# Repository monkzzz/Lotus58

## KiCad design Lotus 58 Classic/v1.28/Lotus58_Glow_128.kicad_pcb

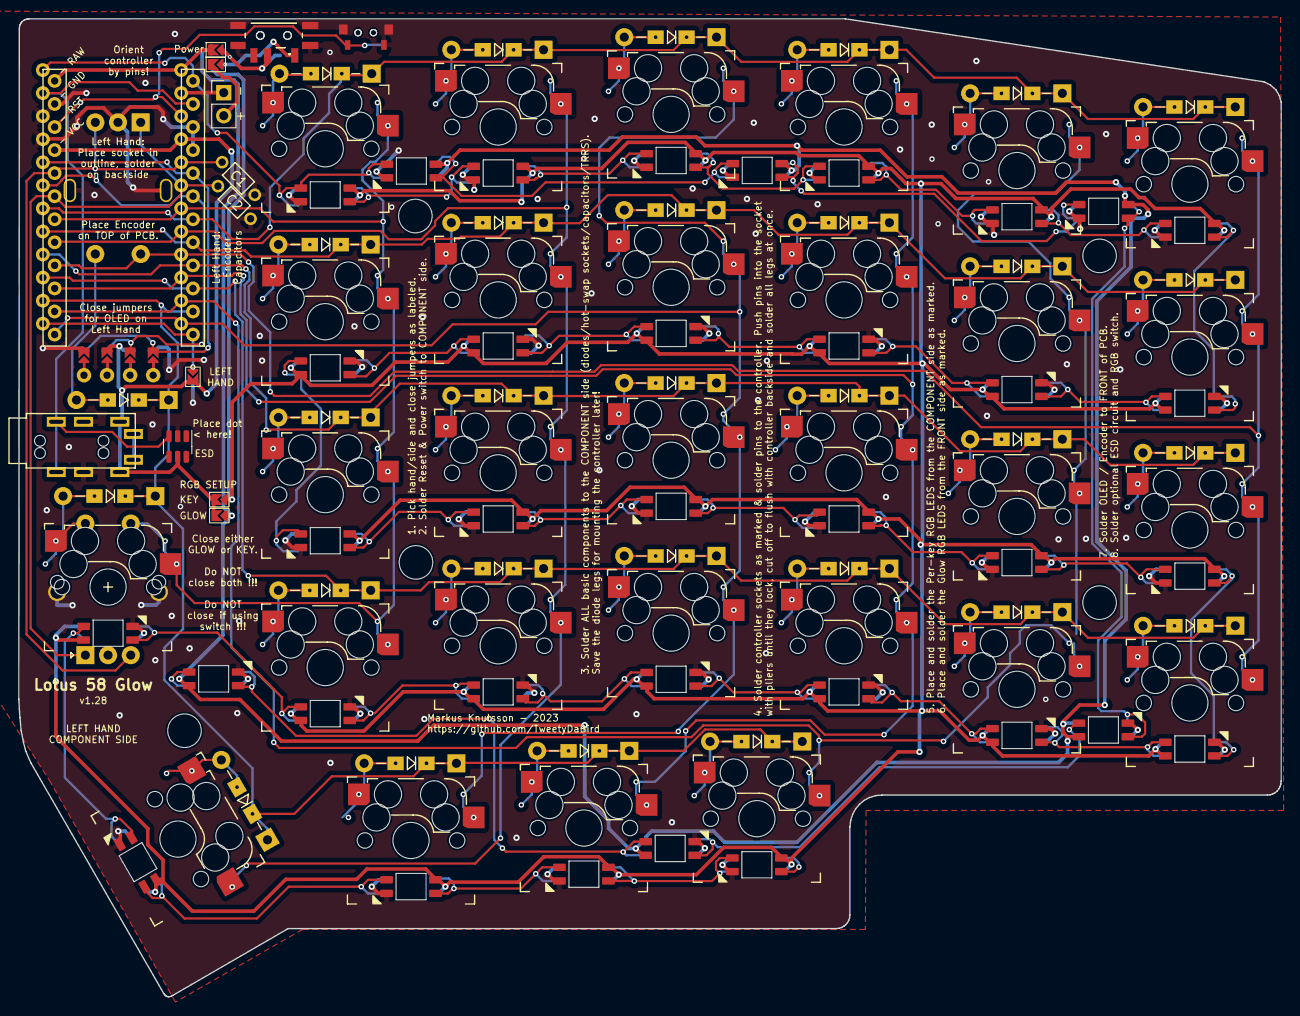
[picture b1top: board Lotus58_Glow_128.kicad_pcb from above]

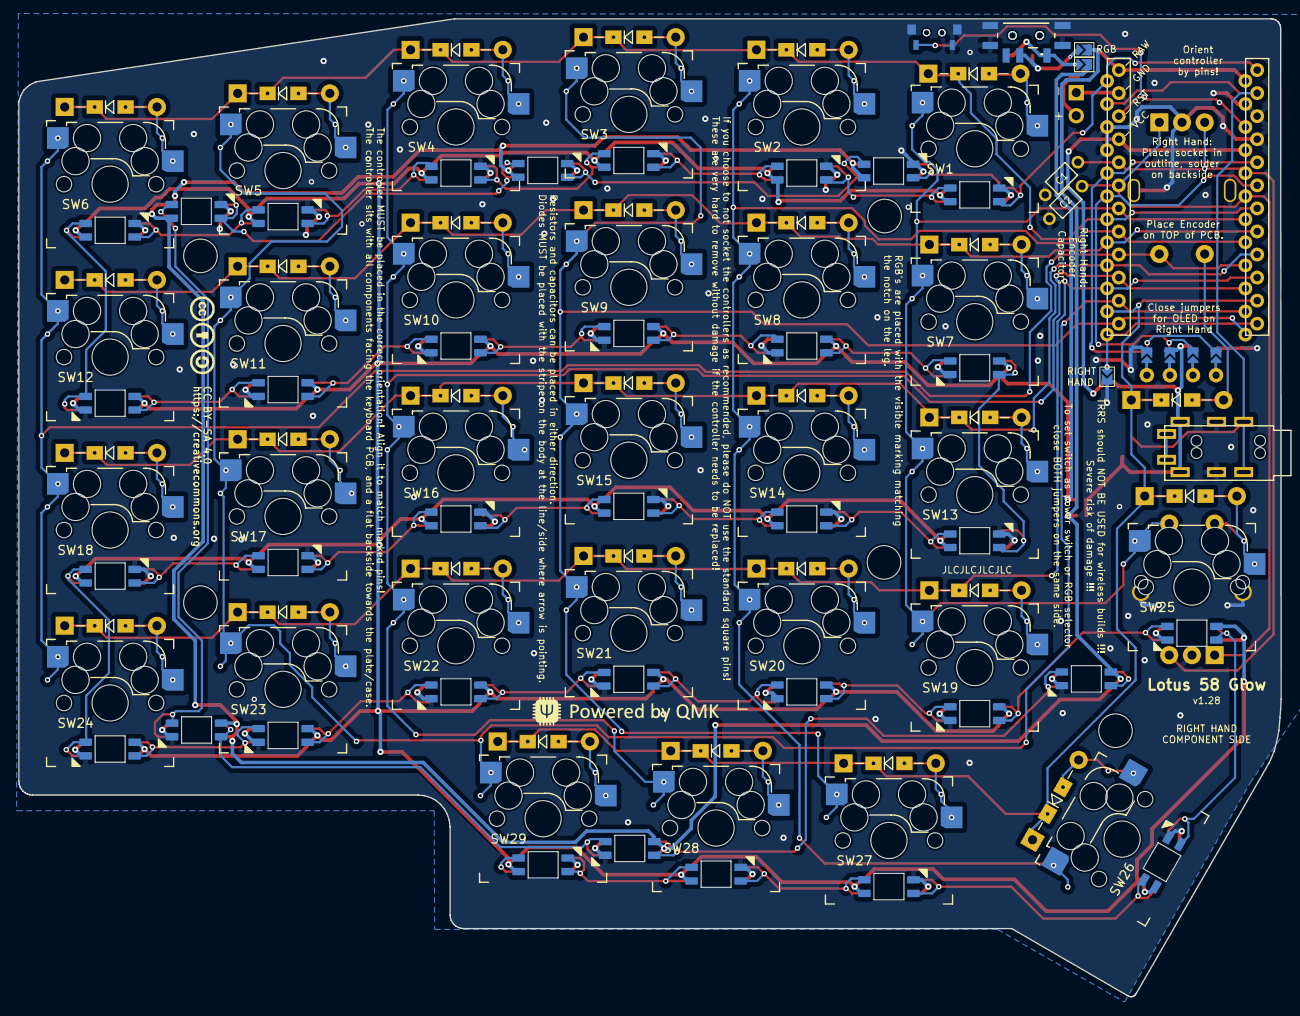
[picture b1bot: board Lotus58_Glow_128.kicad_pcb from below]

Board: 2 copper layers, 139.1 x 107.7 mm, 122 parts (73 on the bottom side), 90 nets.

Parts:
C1, C2: 100nF; RESISTOR_Reversible
D1, D2, D3, D4, D5, D6, D7, D8, D9, D10, D11, D12, D13, D14, D15, D16, D17, D18, D19, D20, D21, D22, D23, D24, D25, D26, D27, D28, D29, D30: 1N4148/1N4148W; Diode_DO35_SOD123
J1: PJ-320A; MJ-4PP-9_alim
J2: Conn_01x02; PinHeader_1x02_P2.54mm_Vertical
JP1, JP4, JP5, JP6, JP7, JP8: FULL; Jumper_min_v2
JP2: LEFT; Jumper_min_v2
JP3: RIGHT; Jumper_min_v2
LED1, LED2, LED3, LED4, LED5, LED6, LED7, LED8, LED9, LED10, LED11, LED12, LED13, LED14, LED15, LED16, LED17, LED18, LED19, LED20, LED21, LED22, LED23, LED24, LED25, LED26, LED27, LED28, LED29, LED30, LED31, LED32, LED33, LED34, LED35: SK6812MINI-E; MX_SK6812MINI-E_REVERSIBLE
Logo1: QMK_Logo; qmk logo
Logo2: CC-BY-SA-4.0; CC_BY_SA_40_line
P1: OLED; SSD1306-0.91-OLED-4pin-128x32 doublesided
RES1, RES2: TS-A002; YTS-A002
S1, S2: MSK12C02
SW1, SW2, SW3, SW4, SW5, SW6, SW7, SW8, SW9, SW10, SW11, SW12, SW13, SW14, SW15, SW16, SW17, SW18, SW19, SW20, SW21, SW22, SW23, SW24, SW25, SW26, SW27, SW28, SW29: Kailh hotswap MX socket; SW_MX_HotSwap_Reversible
SW30: Rotary_Encoder_Switch; RotaryEncoder_Alps_EC11E-Switch_Vertical_H20_special
SW31: Rotary_Encoder_Switch; RotaryEncoder_Alps_EC11E-Switch_Special
TH1, TH2, TH3, TH4, TH5: HOLE; Spacer PCB hole
U1: ProMicro; ProMicro_Reversible_orig
U2: SRV05-4; SOT-23-6

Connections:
/Batt: J2.2, JP4.1
/PWR_GLOW: JP5.2, JP7.1, LED1.1 (VCC), LED2.1 (VCC), LED3.1 (VCC), LED4.1 (VCC), LED5.1 (VCC), LED6.1 (VCC)
/PWR_KEY: JP6.2, JP8.1, LED7.1 (VCC), LED8.1 (VCC), LED9.1 (VCC), LED10.1 (VCC), LED11.1 (VCC), LED12.1 (VCC), LED13.1 (VCC), LED14.1 (VCC), LED15.1 (VCC), LED16.1 (VCC), LED17.1 (VCC), LED18.1 (VCC), LED19.1 (VCC), LED20.1 (VCC), LED21.1 (VCC), LED22.1 (VCC), LED23.1 (VCC), LED24.1 (VCC), LED25.1 (VCC), LED26.1 (VCC), LED27.1 (VCC), LED28.1 (VCC), LED29.1 (VCC), LED30.1 (VCC), LED31.1 (VCC), LED32.1 (VCC), LED33.1 (VCC), LED34.1 (VCC), LED35.1 (VCC)
A: C2.2, SW30.A, SW31.A, U1.19 (A2/PF5)
Alt: D25.2 (A), SW25.2, SW31.S2
B: C1.1, SW30.B, SW31.B, U1.20 (A3/PF4)
Battery: JP1.1, U1.24 (RAW)
DATA: J1.R2, U1.2 (RX1/PD2), U2.3 (IO2)
GND: C1.2, C2.1, J1.R1, J2.1, JP3.1, LED1.3 (GND), LED2.3 (GND), LED3.3 (GND), LED4.3 (GND), LED5.3 (GND), LED6.3 (GND), LED7.3 (GND), LED8.3 (GND), LED9.3 (GND), LED10.3 (GND), LED11.3 (GND), LED12.3 (GND), LED13.3 (GND), LED14.3 (GND), LED15.3 (GND), LED16.3 (GND), LED17.3 (GND), LED18.3 (GND), LED19.3 (GND), LED20.3 (GND), LED21.3 (GND), LED22.3 (GND), LED23.3 (GND), LED24.3 (GND), LED25.3 (GND), LED26.3 (GND), LED27.3 (GND), LED28.3 (GND), LED29.3 (GND), LED30.3 (GND), LED31.3 (GND), LED32.3 (GND), LED33.3 (GND), LED34.3 (GND), LED35.3 (GND), P1.1 (GND), RES1.2, RES1.3, RES2.2, RES2.3, S1.MP (GND), S2.MP (GND), SW30.C, SW30.MP1 (GND), SW30.MP2 (GND), SW31.C, SW31.MP1 (GND), SW31.MP2 (GND), U1.3 (GND), U1.4 (GND), U1.23 (GND), U2.2 (VN)
Hand: JP2.2, JP3.2, U1.12 (9/PB5)
LED: LED1.4 (DIN), LED7.4 (DIN), U1.1 (TX0/PD3)
unnamed: D1.2 (A), SW1.2
unnamed: D2.2 (A), SW2.2
unnamed: D3.2 (A), SW3.2
unnamed: D4.2 (A), SW4.2
unnamed: D5.2 (A), SW5.2
unnamed: D6.2 (A), SW6.2
unnamed: D7.2 (A), SW7.2
unnamed: D8.2 (A), SW8.2
unnamed: D9.2 (A), SW9.2
unnamed: D10.2 (A), SW10.2
unnamed: D11.2 (A), SW11.2
unnamed: D12.2 (A), SW12.2
unnamed: D13.2 (A), SW13.2
unnamed: D14.2 (A), SW14.2
unnamed: D15.2 (A), SW15.2
unnamed: D16.2 (A), SW16.2
unnamed: D17.2 (A), SW17.2
unnamed: D18.2 (A), SW18.2
unnamed: D19.2 (A), SW19.2
unnamed: D20.2 (A), SW20.2
unnamed: D21.2 (A), SW21.2
unnamed: D22.2 (A), SW22.2
unnamed: D23.2 (A), SW23.2
unnamed: D24.2 (A), SW24.2
unnamed: D26.2 (A), SW26.2
unnamed: D27.2 (A), SW27.2
unnamed: D28.2 (A), SW28.2
unnamed: D29.2 (A), SW29.2
unnamed: D30.2 (A), SW30.S1
unnamed: JP1.2, JP7.2, S1.COM, S2.COM
unnamed: JP4.2, JP8.2, S1.NC, S2.NC
unnamed: LED1.2 (DOUT), LED2.4 (DIN)
unnamed: LED2.2 (DOUT), LED3.4 (DIN)
unnamed: LED3.2 (DOUT), LED4.4 (DIN)
unnamed: LED4.2 (DOUT), LED5.4 (DIN)
unnamed: LED5.2 (DOUT), LED6.4 (DIN)
unnamed: LED7.2 (DOUT), LED8.4 (DIN)
unnamed: LED8.2 (DOUT), LED9.4 (DIN)
unnamed: LED9.2 (DOUT), LED10.4 (DIN)
unnamed: LED10.2 (DOUT), LED11.4 (DIN)
unnamed: LED11.2 (DOUT), LED12.4 (DIN)
unnamed: LED12.2 (DOUT), LED18.4 (DIN)
unnamed: LED13.4 (DIN), LED14.2 (DOUT)
unnamed: LED13.2 (DOUT), LED19.4 (DIN)
unnamed: LED14.4 (DIN), LED15.2 (DOUT)
unnamed: LED15.4 (DIN), LED16.2 (DOUT)
unnamed: LED16.4 (DIN), LED17.2 (DOUT)
unnamed: LED17.4 (DIN), LED18.2 (DOUT)
unnamed: LED19.2 (DOUT), LED20.4 (DIN)
unnamed: LED20.2 (DOUT), LED21.4 (DIN)
unnamed: LED21.2 (DOUT), LED22.4 (DIN)
unnamed: LED22.2 (DOUT), LED23.4 (DIN)
unnamed: LED23.2 (DOUT), LED24.4 (DIN)
unnamed: LED24.2 (DOUT), LED30.4 (DIN)
unnamed: LED25.4 (DIN), LED26.2 (DOUT)
unnamed: LED25.2 (DOUT), LED31.4 (DIN)
unnamed: LED26.4 (DIN), LED27.2 (DOUT)
unnamed: LED27.4 (DIN), LED28.2 (DOUT)
unnamed: LED28.4 (DIN), LED29.2 (DOUT)
unnamed: LED29.4 (DIN), LED30.2 (DOUT)
unnamed: LED31.2 (DOUT), LED32.4 (DIN)
unnamed: LED32.2 (DOUT), LED33.4 (DIN)
unnamed: LED33.2 (DOUT), LED34.4 (DIN)
unnamed: LED34.2 (DOUT), LED35.4 (DIN)
RESET: RES1.1, RES2.1, U1.22 (RST)
SCL: P1.3 (SCL), U1.6 (3/PD0)
SDA: P1.4 (SDA), U1.5 (2/PD1)
VCC: J1.T, JP2.1, JP5.1, JP6.1, P1.2 (VCC), U1.21 (VCC), U2.5 (VP)
col0: SW6.1, SW12.1, SW18.1, SW24.1, SW30.S2, U1.16 (15/PB1)
col1: SW5.1, SW11.1, SW17.1, SW23.1, SW29.1, U1.14 (16/PB2)
col2: SW4.1, SW10.1, SW16.1, SW22.1, SW28.1, U1.15 (14/PB3)
col3: SW3.1, SW9.1, SW15.1, SW21.1, SW27.1, U1.13 (10/PB6)
col4: SW2.1, SW8.1, SW14.1, SW20.1, SW26.1, U1.17 (A0/PF7)
col5: SW1.1, SW7.1, SW13.1, SW19.1, SW25.1, SW31.S1, U1.18 (A1/PF6)
row0: D1.1 (K), D2.1 (K), D3.1 (K), D4.1 (K), D5.1 (K), D6.1 (K), U1.7 (4/PD4)
row1: D7.1 (K), D8.1 (K), D9.1 (K), D10.1 (K), D11.1 (K), D12.1 (K), U1.8 (5/PC6)
row2: D13.1 (K), D14.1 (K), D15.1 (K), D16.1 (K), D17.1 (K), D18.1 (K), U1.9 (6/PD7)
row3: D19.1 (K), D20.1 (K), D21.1 (K), D22.1 (K), D23.1 (K), D24.1 (K), U1.10 (7/PE6)
row4: D25.1 (K), D26.1 (K), D27.1 (K), D28.1 (K), D29.1 (K), D30.1 (K), U1.11 (8/PB4)

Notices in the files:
Lotus 58 Classic/v1.28/Lotus58_Glow_128.kicad_pcb:
Licensed under Creative Commons BY-SA 4.0 International
